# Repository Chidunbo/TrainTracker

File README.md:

# TrainTracker
TrainTrackerHardware

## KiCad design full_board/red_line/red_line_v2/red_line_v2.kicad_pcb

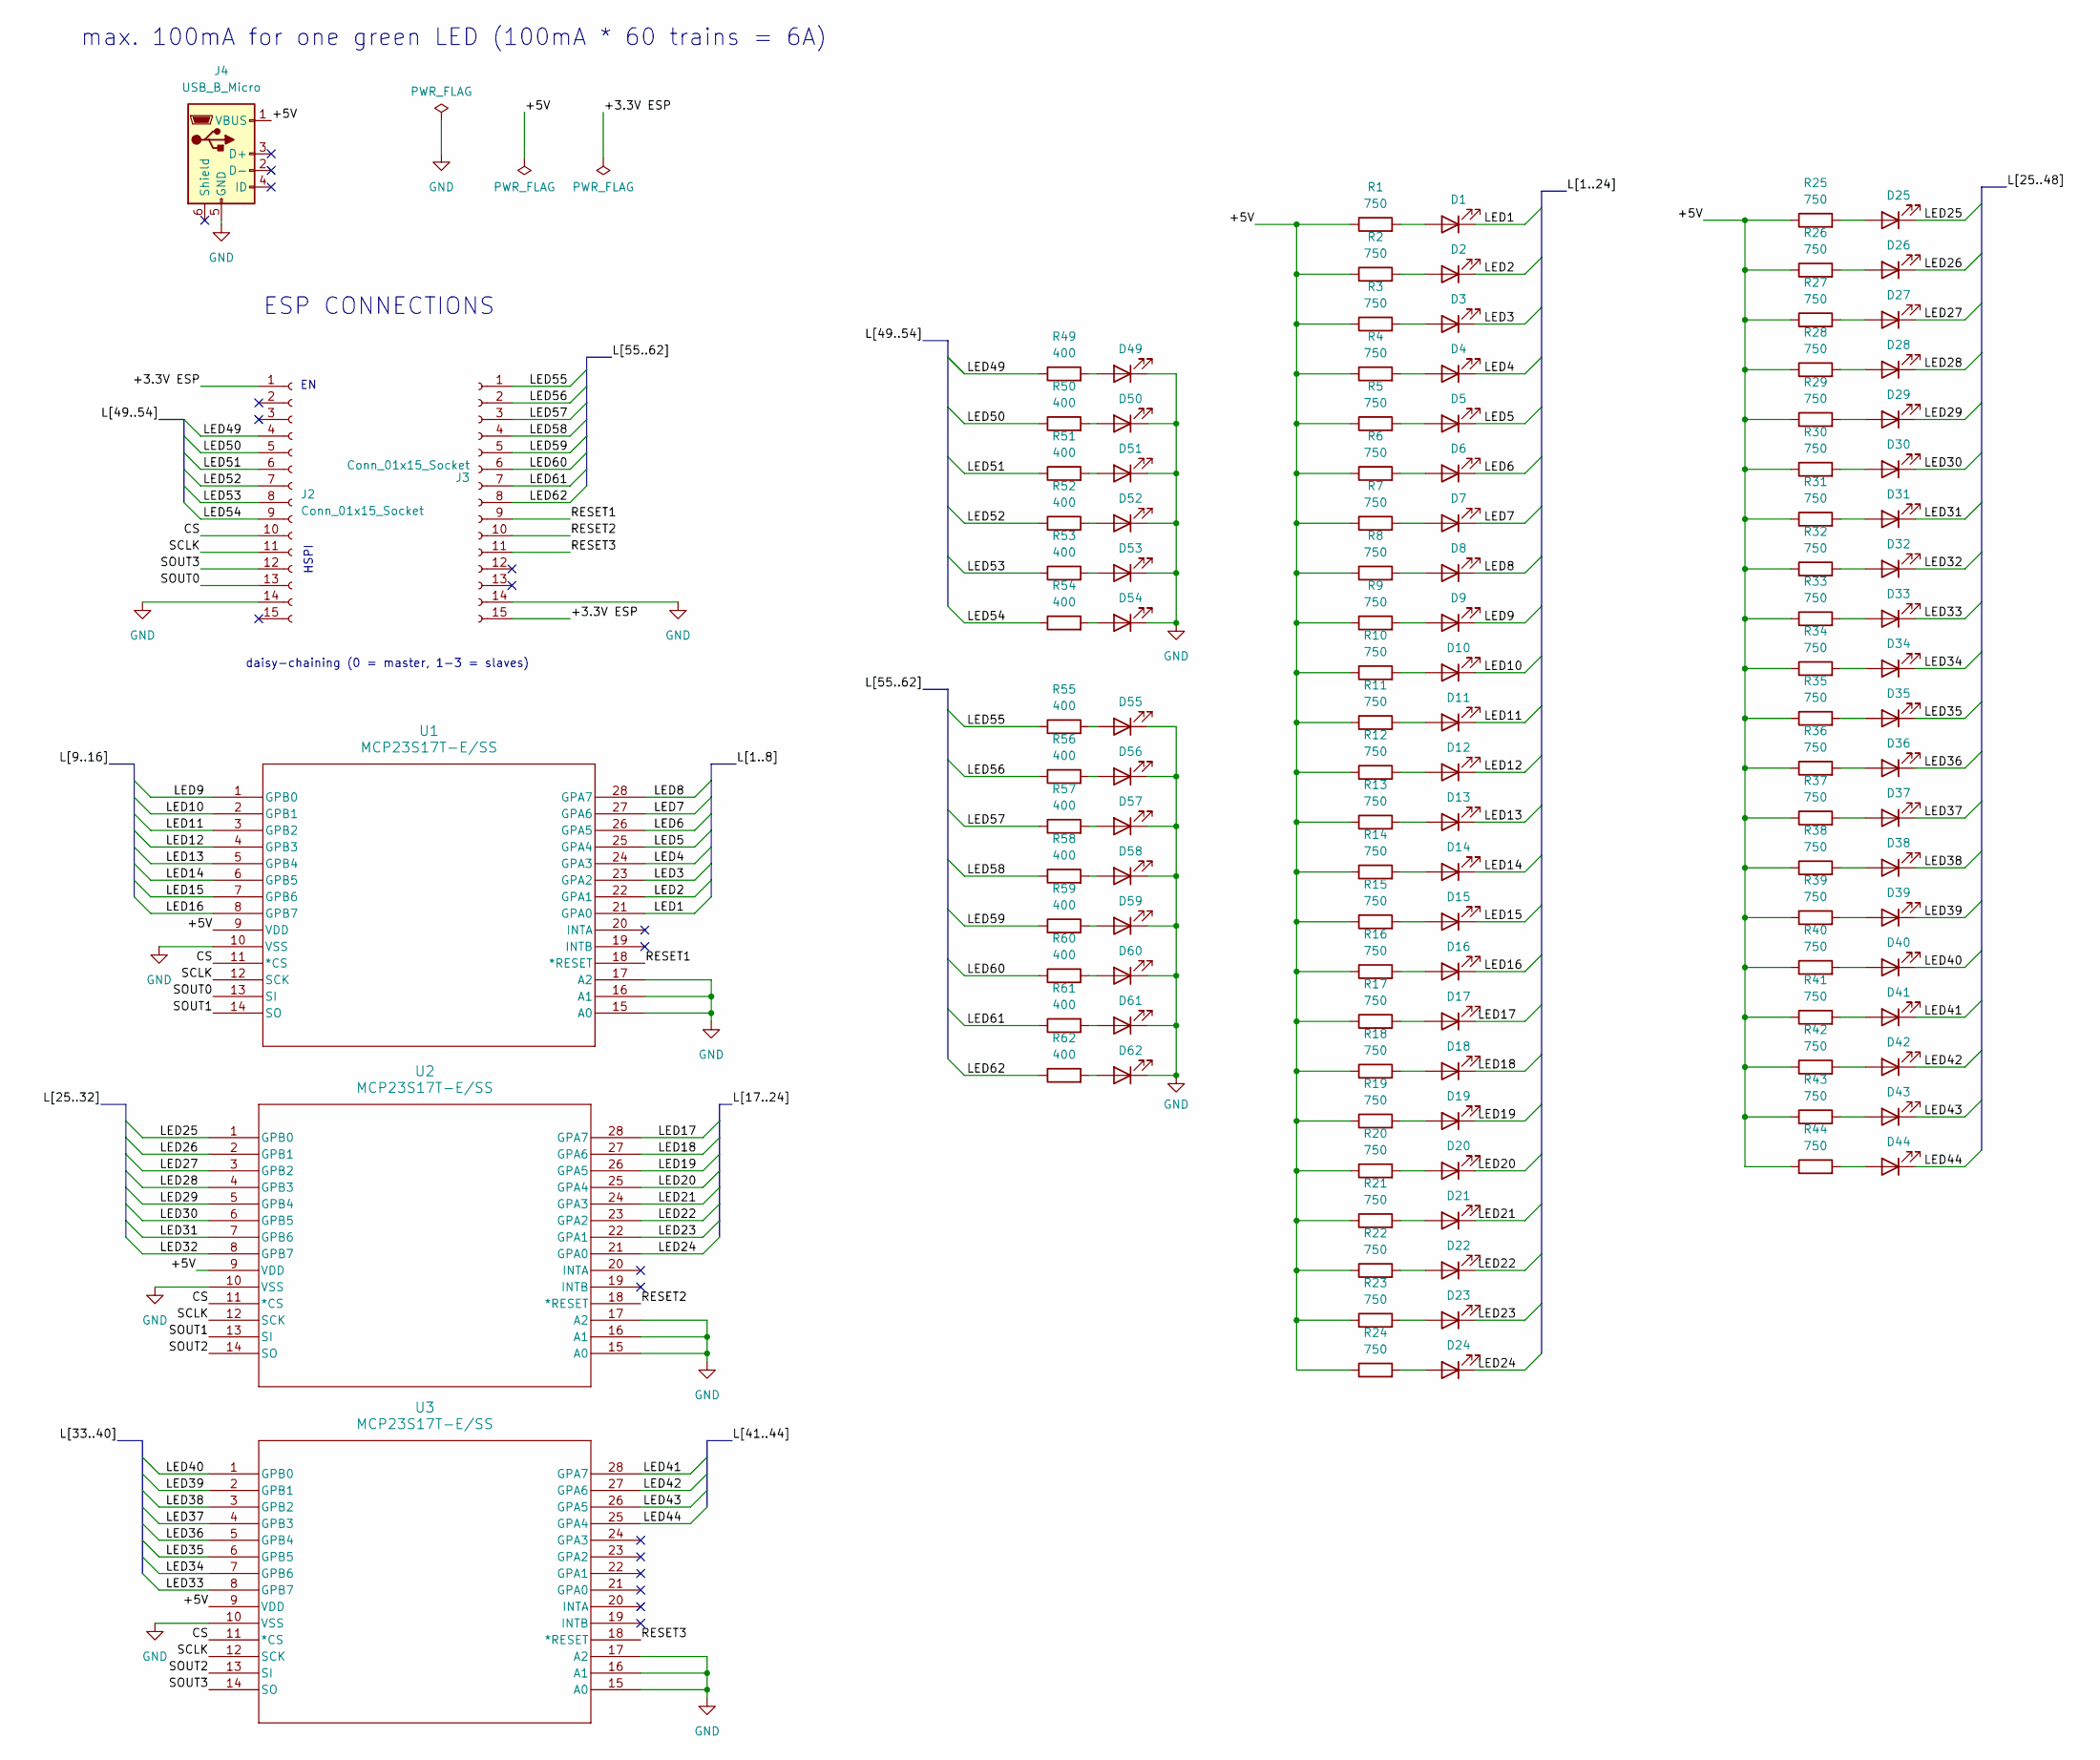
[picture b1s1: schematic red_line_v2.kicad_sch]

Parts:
D1, D2, D3, D4, D5, D6, D7, D8, D9, D10, D11, D12, D13, D14, D15, D16, D17, D18, D19, D20, D21, D22, D23, D24, D25, D26, D27, D28, D29, D30, D31, D32, D33, D34, D35, D36, D37, D38, D39, D40, D41, D42, D43, D44, D49, D50, D51, D52, D53, D54, D55, D56, D57, D58, D59, D60, D61, D62: LED; LED_0603_1608Metric
J2, J3: Conn_01x15_Socket; PinHeader_1x15_P2.54mm_Vertical
J4: USB_B_Micro; USB_Micro-B_Molex-105017-0001
R1, R2, R3, R4, R5, R6, R7, R8, R9, R10, R11, R12, R13, R14, R15, R16, R17, R18, R19, R20, R21, R22, R23, R24, R25, R26, R27, R28, R29, R30, R31, R32, R33, R34, R35, R36, R37, R38, R39, R40, R41, R42, R43, R44: 750; R_0603_1608Metric
R49, R50, R51, R52, R53, R54, R55, R56, R57, R58, R59, R60, R61, R62: 400; R_0603_1608Metric
U1, U2, U3: MCP23S17T-E/SS; SSOP28_MC_MCH

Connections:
/+3.3V ESP: J2.1, J3.15
/+5V: J4.1 (VBUS), R1.1, R2.1, R3.1, R4.1, R5.1, R6.1, R7.1, R8.1, R9.1, R10.1, R11.1, R12.1, R13.1, R14.1, R15.1, R16.1, R17.1, R18.1, R19.1, R20.1, R21.1, R22.1, R23.1, R24.1, R25.1, R26.1, R27.1, R28.1, R29.1, R30.1, R31.1, R32.1, R33.1, R34.1, R35.1, R36.1, R37.1, R38.1, R39.1, R40.1, R41.1, R42.1, R43.1, R44.1, U1.9 (VDD), U2.9 (VDD), U3.9 (VDD)
/CS: J2.10, U1.11 (*CS), U2.11 (*CS), U3.11 (*CS)
/LED1: D1.1 (K), U1.21 (GPA0)
/LED2: D2.1 (K), U1.22 (GPA1)
/LED3: D3.1 (K), U1.23 (GPA2)
/LED4: D4.1 (K), U1.24 (GPA3)
/LED5: D5.1 (K), U1.25 (GPA4)
/LED6: D6.1 (K), U1.26 (GPA5)
/LED7: D7.1 (K), U1.27 (GPA6)
/LED8: D8.1 (K), U1.28 (GPA7)
/LED9: D9.1 (K), U1.1 (GPB0)
/LED10: D10.1 (K), U1.2 (GPB1)
/LED11: D11.1 (K), U1.3 (GPB2)
/LED12: D12.1 (K), U1.4 (GPB3)
/LED13: D13.1 (K), U1.5 (GPB4)
/LED14: D14.1 (K), U1.6 (GPB5)
/LED15: D15.1 (K), U1.7 (GPB6)
/LED16: D16.1 (K), U1.8 (GPB7)
/LED17: D17.1 (K), U2.28 (GPA7)
/LED18: D18.1 (K), U2.27 (GPA6)
/LED19: D19.1 (K), U2.26 (GPA5)
/LED20: D20.1 (K), U2.25 (GPA4)
/LED21: D21.1 (K), U2.24 (GPA3)
/LED22: D22.1 (K), U2.23 (GPA2)
/LED23: D23.1 (K), U2.22 (GPA1)
/LED24: D24.1 (K), U2.21 (GPA0)
/LED25: D25.1 (K), U2.1 (GPB0)
/LED26: D26.1 (K), U2.2 (GPB1)
/LED27: D27.1 (K), U2.3 (GPB2)
/LED28: D28.1 (K), U2.4 (GPB3)
/LED29: D29.1 (K), U2.5 (GPB4)
/LED30: D30.1 (K), U2.6 (GPB5)
/LED31: D31.1 (K), U2.7 (GPB6)
/LED32: D32.1 (K), U2.8 (GPB7)
/LED33: D33.1 (K), U3.8 (GPB7)
/LED34: D34.1 (K), U3.7 (GPB6)
/LED35: D35.1 (K), U3.6 (GPB5)
/LED36: D36.1 (K), U3.5 (GPB4)
/LED37: D37.1 (K), U3.4 (GPB3)
/LED38: D38.1 (K), U3.3 (GPB2)
/LED39: D39.1 (K), U3.2 (GPB1)
/LED40: D40.1 (K), U3.1 (GPB0)
/LED41: D41.1 (K), U3.28 (GPA7)
/LED42: D42.1 (K), U3.27 (GPA6)
/LED43: D43.1 (K), U3.26 (GPA5)
/LED44: D44.1 (K), U3.25 (GPA4)
/LED49: J2.4, R49.1
/LED50: J2.5, R50.1
/LED51: J2.6, R51.1
/LED52: J2.7, R52.1
/LED53: J2.8, R53.1
/LED54: J2.9, R54.1
/LED55: J3.1, R55.1
/LED56: J3.2, R56.1
/LED57: J3.3, R57.1
/LED58: J3.4, R58.1
/LED59: J3.5, R59.1
/LED60: J3.6, R60.1
/LED61: J3.7, R61.1
/LED62: J3.8, R62.1
/RESET1: J3.9, U1.18 (*RESET)
/RESET2: J3.10, U2.18 (*RESET)
/RESET3: J3.11, U3.18 (*RESET)
/SCLK: J2.11, U1.12 (SCK), U2.12 (SCK), U3.12 (SCK)
/SOUT0: J2.13, U1.13 (SI)
/SOUT1: U1.14 (SO), U2.13 (SI)
/SOUT2: U2.14 (SO), U3.13 (SI)
/SOUT3: J2.12, U3.14 (SO)
GND: D49.1 (K), D50.1 (K), D51.1 (K), D52.1 (K), D53.1 (K), D54.1 (K), D55.1 (K), D56.1 (K), D57.1 (K), D58.1 (K), D59.1 (K), D60.1 (K), D61.1 (K), D62.1 (K), J2.14, J3.14, J4.5 (GND), U1.10 (VSS), U1.15 (A0), U1.16 (A1), U1.17 (A2), U2.10 (VSS), U2.15 (A0), U2.16 (A1), U2.17 (A2), U3.10 (VSS), U3.15 (A0), U3.16 (A1), U3.17 (A2)
unnamed: D1.2 (A), R1.2
unnamed: D2.2 (A), R2.2
unnamed: D3.2 (A), R3.2
unnamed: D4.2 (A), R4.2
unnamed: D5.2 (A), R5.2
unnamed: D6.2 (A), R6.2
unnamed: D7.2 (A), R7.2
unnamed: D8.2 (A), R8.2
unnamed: D9.2 (A), R9.2
unnamed: D10.2 (A), R10.2
unnamed: D11.2 (A), R11.2
unnamed: D12.2 (A), R12.2
unnamed: D13.2 (A), R13.2
unnamed: D14.2 (A), R14.2
unnamed: D15.2 (A), R15.2
unnamed: D16.2 (A), R16.2
unnamed: D17.2 (A), R17.2
unnamed: D18.2 (A), R18.2
unnamed: D19.2 (A), R19.2
unnamed: D20.2 (A), R20.2
unnamed: D21.2 (A), R21.2
unnamed: D22.2 (A), R22.2
unnamed: D23.2 (A), R23.2
unnamed: D24.2 (A), R24.2
unnamed: D25.2 (A), R25.2
unnamed: D26.2 (A), R26.2
unnamed: D27.2 (A), R27.2
unnamed: D28.2 (A), R28.2
unnamed: D29.2 (A), R29.2
unnamed: D30.2 (A), R30.2
unnamed: D31.2 (A), R31.2
unnamed: D32.2 (A), R32.2
unnamed: D33.2 (A), R33.2
unnamed: D34.2 (A), R34.2
unnamed: D35.2 (A), R35.2
unnamed: D36.2 (A), R36.2
unnamed: D37.2 (A), R37.2
unnamed: D38.2 (A), R38.2
unnamed: D39.2 (A), R39.2
unnamed: D40.2 (A), R40.2
unnamed: D41.2 (A), R41.2
unnamed: D42.2 (A), R42.2
unnamed: D43.2 (A), R43.2
unnamed: D44.2 (A), R44.2
unnamed: D49.2 (A), R49.2
unnamed: D50.2 (A), R50.2
unnamed: D51.2 (A), R51.2
unnamed: D52.2 (A), R52.2
unnamed: D53.2 (A), R53.2
unnamed: D54.2 (A), R54.2
unnamed: D55.2 (A), R55.2
unnamed: D56.2 (A), R56.2
unnamed: D57.2 (A), R57.2
unnamed: D58.2 (A), R58.2
unnamed: D59.2 (A), R59.2
unnamed: D60.2 (A), R60.2
unnamed: D61.2 (A), R61.2
unnamed: D62.2 (A), R62.2

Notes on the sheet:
HSPI
max. 100mA for one green LED (100mA * 60 trains = 6A)
ESP CONNECTIONS
daisy-chaining (0 = master, 1-3 = slaves)

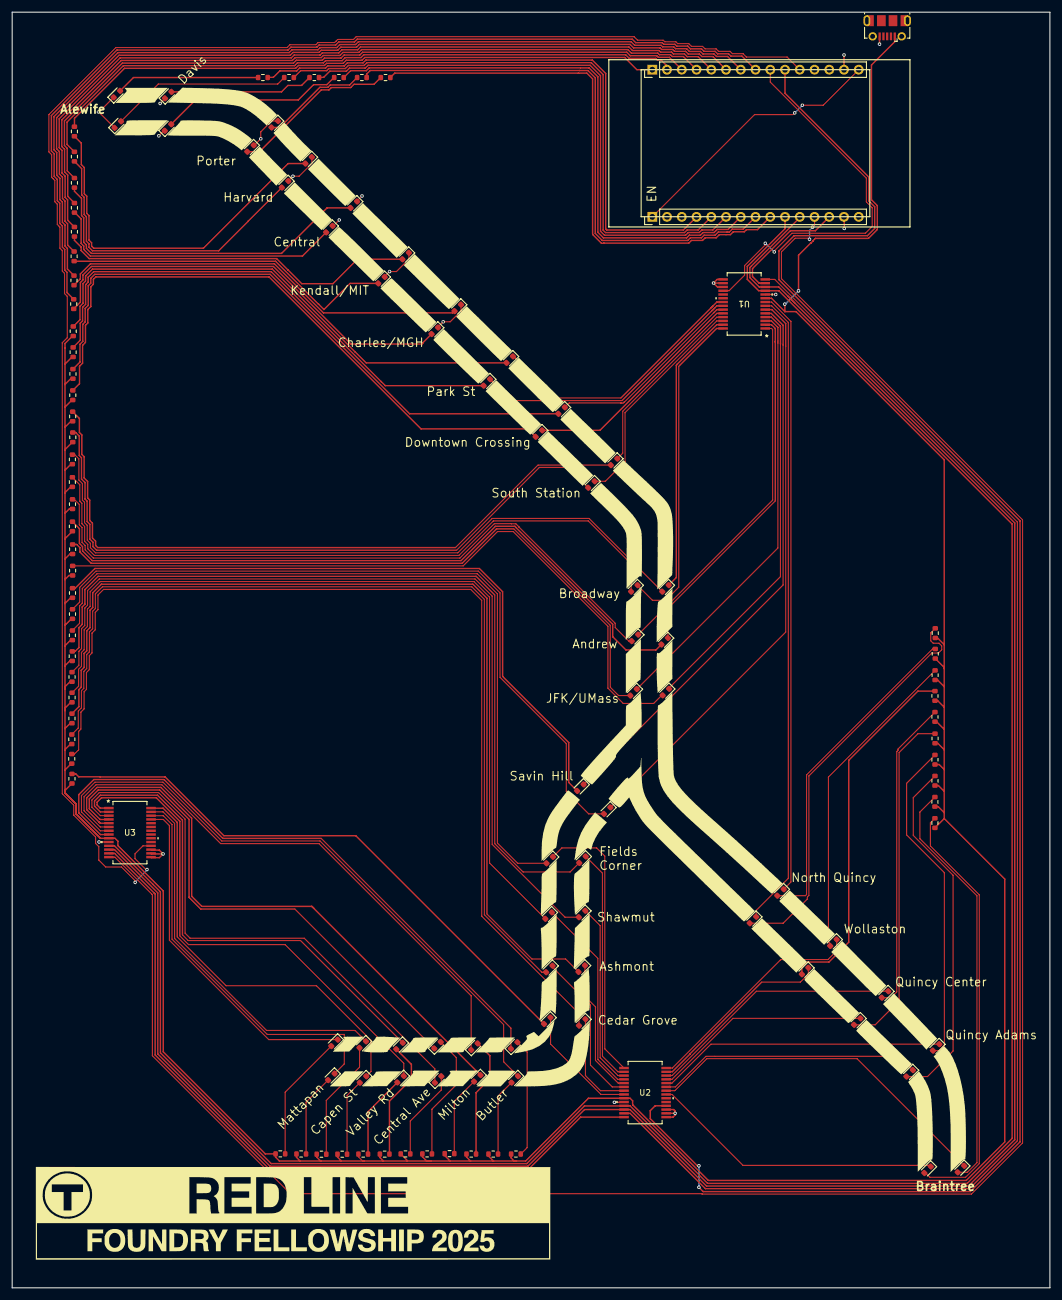
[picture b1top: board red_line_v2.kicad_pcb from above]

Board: 2 copper layers, 178.7 x 219.7 mm, 122 parts (0 on the bottom side), 128 nets.

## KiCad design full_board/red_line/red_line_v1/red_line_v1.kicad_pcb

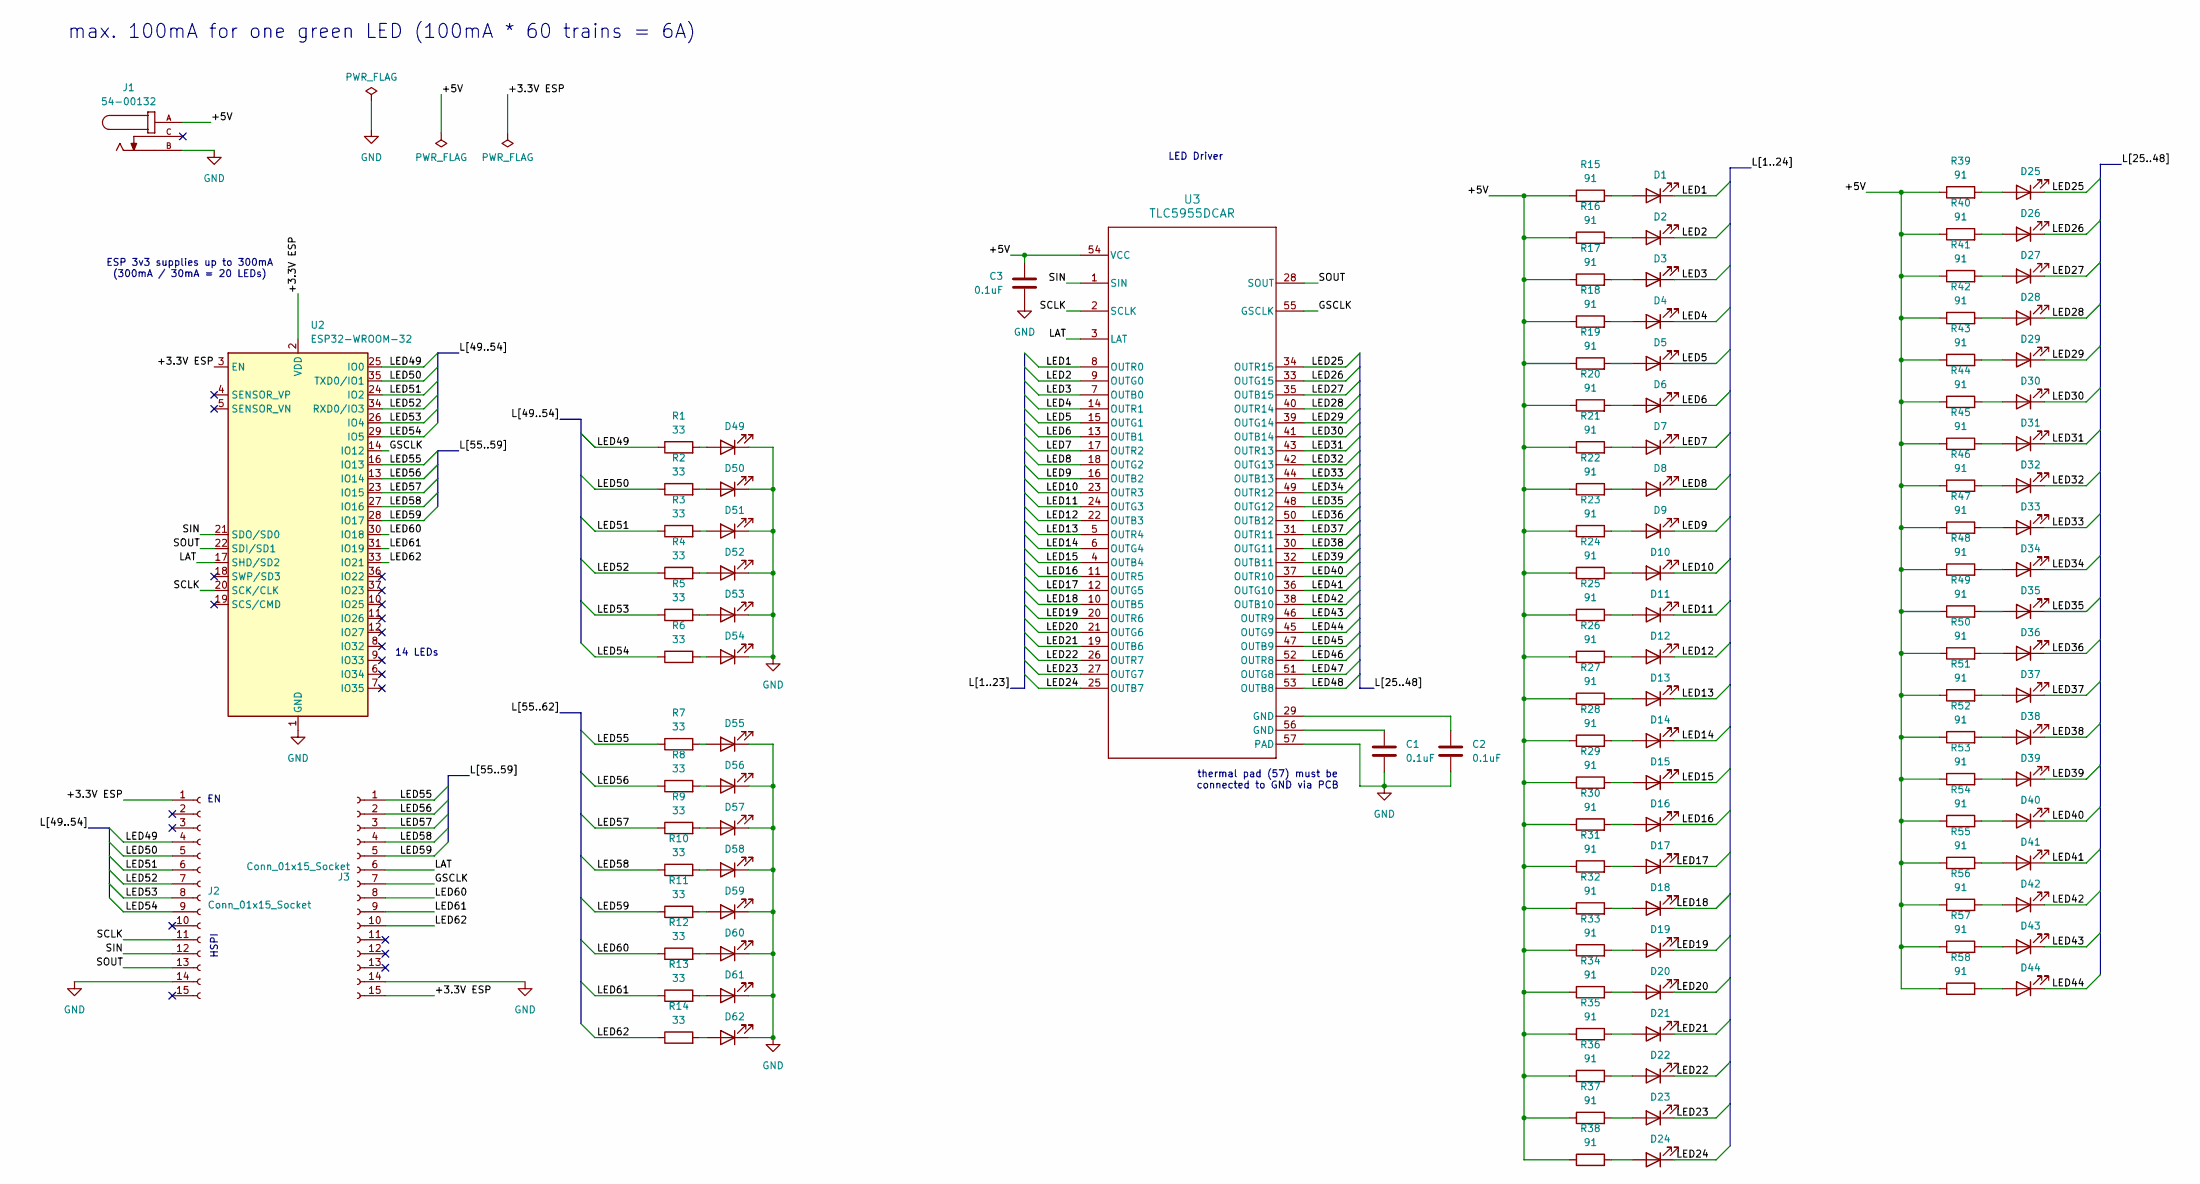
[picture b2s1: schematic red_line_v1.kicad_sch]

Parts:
C1, C2, C3: 0.1uF; C_0603
D1, D2, D3, D4, D5, D6, D7, D8, D9, D10, D11, D12, D13, D14, D15, D16, D17, D18, D19, D20, D21, D22, D23, D24, D25, D26, D27, D28, D29, D30, D31, D32, D33, D34, D35, D36, D37, D38, D39, D40, D41, D42, D43, D44, D49, D50, D51, D52, D53, D54, D55, D56, D57, D58, D59, D60, D61, D62: LED; LED_0603_1608Metric
J1: 54-00132; TENSILITY_54-00132; PARTREV A
J2, J3: Conn_01x15_Socket; PinHeader_1x15_P2.54mm_Vertical
R1, R2, R3, R4, R5, R6, R7, R8, R9, R10, R11, R12, R13, R14: 33; R_Axial_DIN0207_L6.3mm_D2.5mm_P2.54mm_Vertical
R15, R16, R17, R18, R19, R20, R21, R22, R23, R24, R25, R26, R27, R28, R29, R30, R31, R32, R33, R34, R35, R36, R37, R38, R39, R40, R41, R42, R43, R44, R45, R46, R47, R48, R49, R50, R51, R52, R53, R54, R55, R56, R57, R58: 91; R_Axial_DIN0207_L6.3mm_D2.5mm_P2.54mm_Vertical
U2: ESP32-WROOM-32
U3: TLC5955DCAR; DCA0056F_N

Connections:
/+3.3V ESP: J2.1, J3.15, U2.2 (VDD), U2.3 (EN)
/+5V: C3.2, J1.A, R15.1, R16.1, R17.1, R18.1, R19.1, R20.1, R21.1, R22.1, R23.1, R24.1, R25.1, R26.1, R27.1, R28.1, R29.1, R30.1, R31.1, R32.1, R33.1, R34.1, R35.1, R36.1, R37.1, R38.1, R39.1, R40.1, R41.1, R42.1, R43.1, R44.1, R45.1, R46.1, R47.1, R48.1, R49.1, R50.1, R51.1, R52.1, R53.1, R54.1, R55.1, R56.1, R57.1, R58.1, U3.54 (VCC)
/GSCLK: J3.7, U2.14 (IO12), U3.55 (GSCLK)
/LAT: J3.6, U2.17 (SHD/SD2), U3.3 (LAT)
/LED1: D1.1 (K), U3.8 (OUTR0)
/LED2: D2.1 (K), U3.9 (OUTG0)
/LED3: D3.1 (K), U3.7 (OUTB0)
/LED4: D4.1 (K), U3.14 (OUTR1)
/LED5: D5.1 (K), U3.15 (OUTG1)
/LED6: D6.1 (K), U3.13 (OUTB1)
/LED7: D7.1 (K), U3.17 (OUTR2)
/LED8: D8.1 (K), U3.18 (OUTG2)
/LED9: D9.1 (K), U3.16 (OUTB2)
/LED10: D10.1 (K), U3.23 (OUTR3)
/LED11: D11.1 (K), U3.24 (OUTG3)
/LED12: D12.1 (K), U3.22 (OUTB3)
/LED13: D13.1 (K), U3.5 (OUTR4)
/LED14: D14.1 (K), U3.6 (OUTG4)
/LED15: D15.1 (K), U3.4 (OUTB4)
/LED16: D16.1 (K), U3.11 (OUTR5)
/LED17: D17.1 (K), U3.12 (OUTG5)
/LED18: D18.1 (K), U3.10 (OUTB5)
/LED19: D19.1 (K), U3.20 (OUTR6)
/LED20: D20.1 (K), U3.21 (OUTG6)
/LED21: D21.1 (K), U3.19 (OUTB6)
/LED22: D22.1 (K), U3.26 (OUTR7)
/LED23: D23.1 (K), U3.27 (OUTG7)
/LED24: D24.1 (K), U3.25 (OUTB7)
/LED25: D25.1 (K), U3.34 (OUTR15)
/LED26: D26.1 (K), U3.33 (OUTG15)
/LED27: D27.1 (K), U3.35 (OUTB15)
/LED28: D28.1 (K), U3.40 (OUTR14)
/LED29: D29.1 (K), U3.39 (OUTG14)
/LED30: D30.1 (K), U3.41 (OUTB14)
/LED31: D31.1 (K), U3.43 (OUTR13)
/LED32: D32.1 (K), U3.42 (OUTG13)
/LED33: D33.1 (K), U3.44 (OUTB13)
/LED34: D34.1 (K), U3.49 (OUTR12)
/LED35: D35.1 (K), U3.48 (OUTG12)
/LED36: D36.1 (K), U3.50 (OUTB12)
/LED37: D37.1 (K), U3.31 (OUTR11)
/LED38: D38.1 (K), U3.30 (OUTG11)
/LED39: D39.1 (K), U3.32 (OUTB11)
/LED40: D40.1 (K), U3.37 (OUTR10)
/LED41: D41.1 (K), U3.36 (OUTG10)
/LED42: D42.1 (K), U3.38 (OUTB10)
/LED43: D43.1 (K), U3.46 (OUTR9)
/LED44: D44.1 (K), U3.45 (OUTG9)
/LED45: U3.47 (OUTB9)
/LED46: U3.52 (OUTR8)
/LED47: U3.51 (OUTG8)
/LED48: U3.53 (OUTB8)
/LED49: J2.4, R1.1, U2.25 (IO0)
/LED50: J2.5, R2.1, U2.35 (TXD0/IO1)
/LED51: J2.6, R3.1, U2.24 (IO2)
/LED52: J2.7, R4.1, U2.34 (RXD0/IO3)
/LED53: J2.8, R5.1, U2.26 (IO4)
/LED54: J2.9, R6.1, U2.29 (IO5)
/LED55: J3.1, R7.1, U2.16 (IO13)
/LED56: J3.2, R8.1, U2.13 (IO14)
/LED57: J3.3, R9.1, U2.23 (IO15)
/LED58: J3.4, R10.1, U2.27 (IO16)
/LED59: J3.5, R11.1, U2.28 (IO17)
/LED60: J3.8, R12.1, U2.30 (IO18)
/LED61: J3.9, R13.1, U2.31 (IO19)
/LED62: J3.10, R14.1, U2.33 (IO21)
/SCLK: J2.11, U2.20 (SCK/CLK), U3.2 (SCLK)
/SIN: J2.12, U2.21 (SDO/SD0), U3.1 (SIN)
/SOUT: J2.13, U2.22 (SDI/SD1), U3.28 (SOUT)
GND: C1.1, C2.1, C3.1, D49.1 (K), D50.1 (K), D51.1 (K), D52.1 (K), D53.1 (K), D54.1 (K), D55.1 (K), D56.1 (K), D57.1 (K), D58.1 (K), D59.1 (K), D60.1 (K), D61.1 (K), D62.1 (K), J1.B, J2.14, J3.14, U2.1 (GND), U2.15 (GND), U2.38 (GND), U2.39 (GND), U3.57 (PAD)
unnamed: C1.2, U3.56 (GND)
unnamed: C2.2, U3.29 (GND)
unnamed: D1.2 (A), R15.2
unnamed: D2.2 (A), R16.2
unnamed: D3.2 (A), R17.2
unnamed: D4.2 (A), R18.2
unnamed: D5.2 (A), R19.2
unnamed: D6.2 (A), R20.2
unnamed: D7.2 (A), R21.2
unnamed: D8.2 (A), R22.2
unnamed: D9.2 (A), R23.2
unnamed: D10.2 (A), R24.2
unnamed: D11.2 (A), R25.2
unnamed: D12.2 (A), R26.2
unnamed: D13.2 (A), R27.2
unnamed: D14.2 (A), R28.2
unnamed: D15.2 (A), R29.2
unnamed: D16.2 (A), R30.2
unnamed: D17.2 (A), R31.2
unnamed: D18.2 (A), R32.2
unnamed: D19.2 (A), R33.2
unnamed: D20.2 (A), R34.2
unnamed: D21.2 (A), R35.2
unnamed: D22.2 (A), R36.2
unnamed: D23.2 (A), R37.2
unnamed: D24.2 (A), R38.2
unnamed: D25.2 (A), R39.2
unnamed: D26.2 (A), R40.2
unnamed: D27.2 (A), R41.2
unnamed: D28.2 (A), R42.2
unnamed: D29.2 (A), R43.2
unnamed: D30.2 (A), R44.2
unnamed: D31.2 (A), R45.2
unnamed: D32.2 (A), R46.2
unnamed: D33.2 (A), R47.2
unnamed: D34.2 (A), R48.2
unnamed: D35.2 (A), R49.2
unnamed: D36.2 (A), R50.2
unnamed: D37.2 (A), R51.2
unnamed: D38.2 (A), R52.2
unnamed: D39.2 (A), R53.2
unnamed: D40.2 (A), R54.2
unnamed: D41.2 (A), R55.2
unnamed: D42.2 (A), R56.2
unnamed: D43.2 (A), R57.2
unnamed: D44.2 (A), R58.2
unnamed: D49.2 (A), R1.2
unnamed: D50.2 (A), R2.2
unnamed: D51.2 (A), R3.2
unnamed: D52.2 (A), R4.2
unnamed: D53.2 (A), R5.2
unnamed: D54.2 (A), R6.2
unnamed: D55.2 (A), R7.2
unnamed: D56.2 (A), R8.2
unnamed: D57.2 (A), R9.2
unnamed: D58.2 (A), R10.2
unnamed: D59.2 (A), R11.2
unnamed: D60.2 (A), R12.2
unnamed: D61.2 (A), R13.2
unnamed: D62.2 (A), R14.2

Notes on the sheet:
HSPI
14 LEDs
max. 100mA for one green LED (100mA * 60 trains = 6A)
thermal pad (57) must be connected to GND via PCB
LED Driver
ESP 3v3 supplies up to 300mA (300mA / 30mA = 20 LEDs)

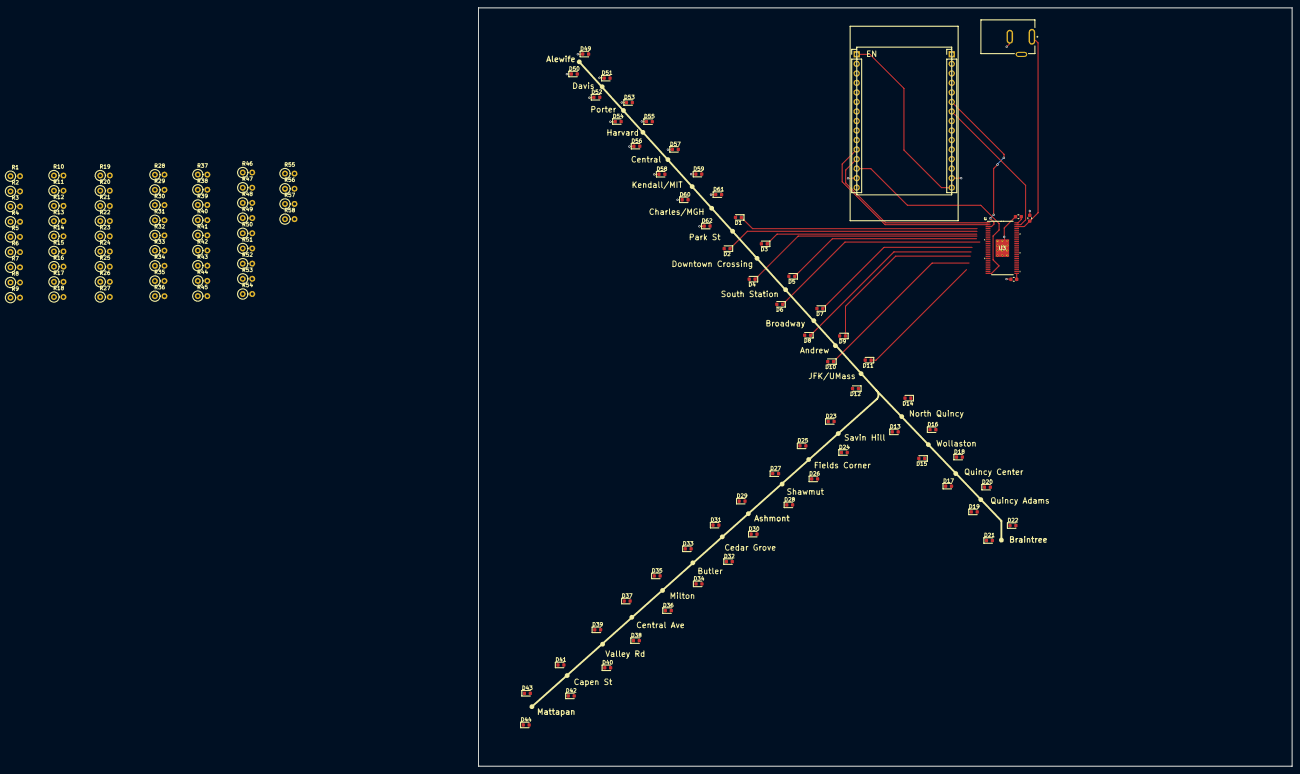
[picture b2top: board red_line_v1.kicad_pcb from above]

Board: 2 copper layers, 217.0 x 202.3 mm, 123 parts (0 on the bottom side), 126 nets.

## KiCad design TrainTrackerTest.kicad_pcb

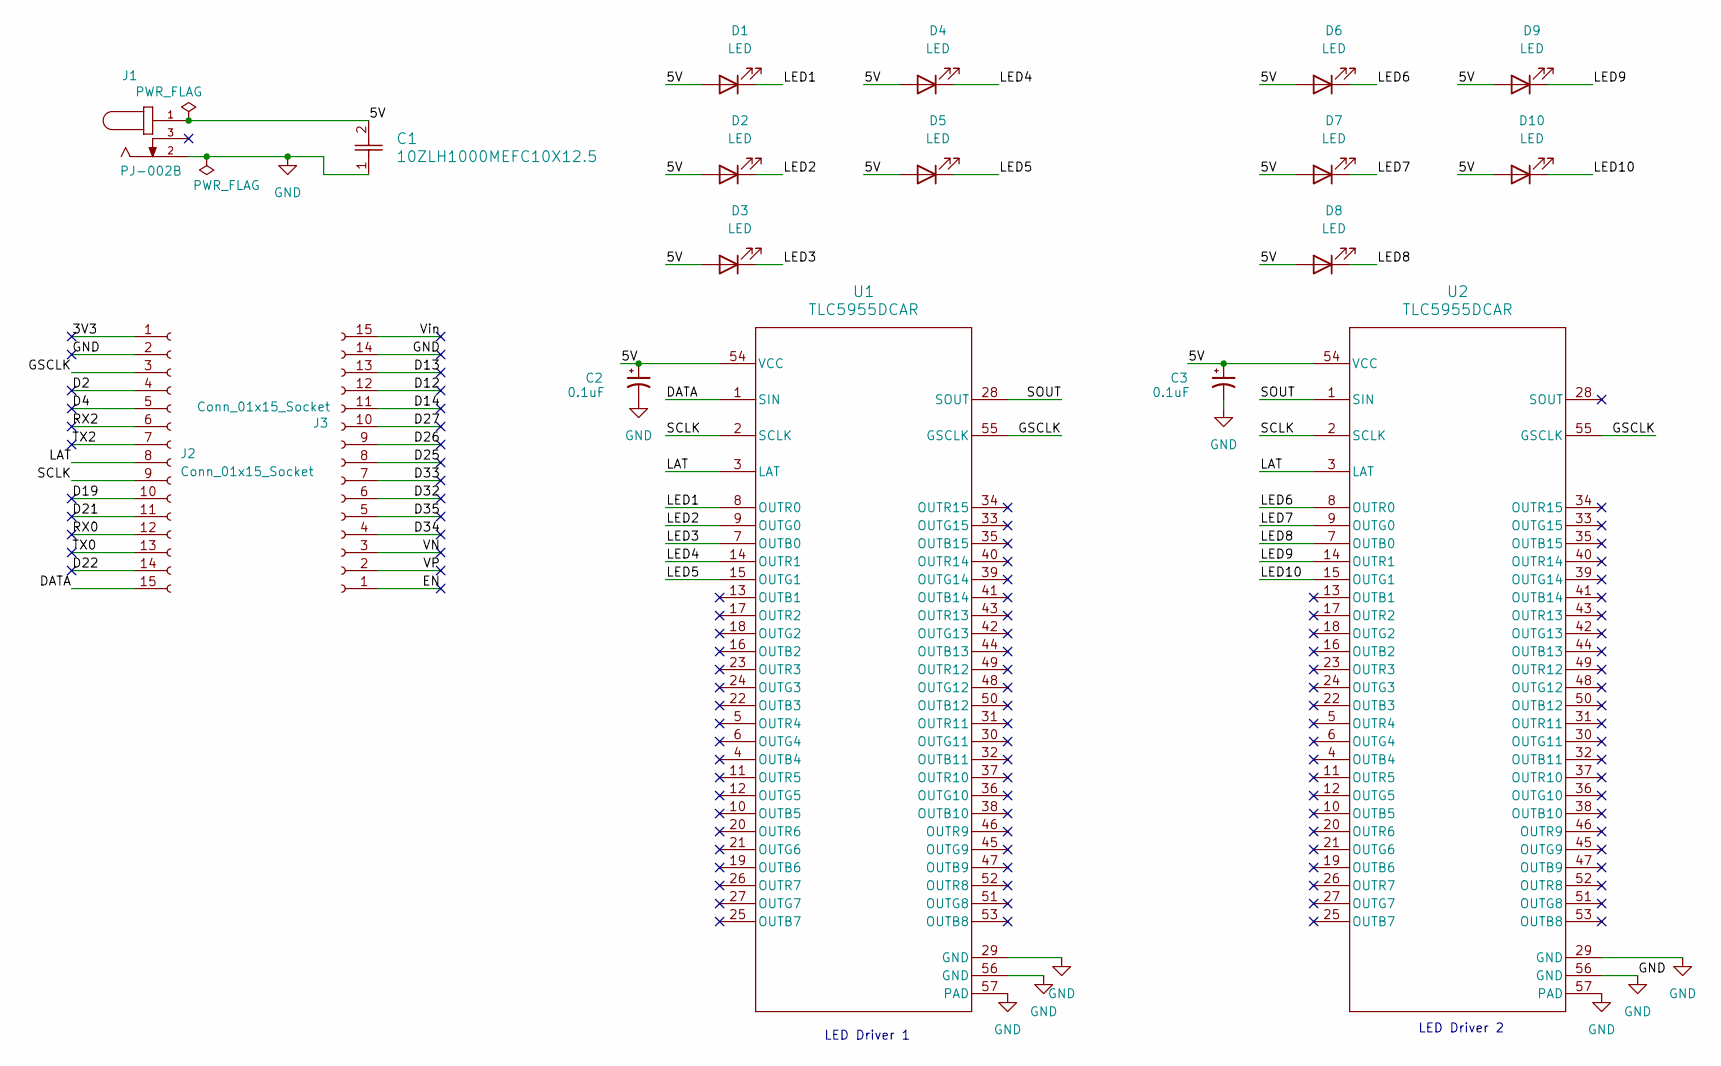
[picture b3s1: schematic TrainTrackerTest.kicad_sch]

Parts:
C1: 10ZLH1000MEFC10X12.5; CAP_10X12.5_RUB
C2, C3: 0.1uF; C_0603_1608Metric
D1, D2, D3, D4, D5, D6, D7, D8, D9, D10: LED; LED_0603_1608Metric
J1: PJ-002B; CUI_PJ-002B
J2, J3: Conn_01x15_Socket; PinHeader_1x15_P2.54mm_Vertical
U1, U2: TLC5955DCAR; DCA0056F_N

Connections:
/3V3: J2.1
/5V: C1.2, C2.1, C3.1, D1.2 (A), D2.2 (A), D3.2 (A), D4.2 (A), D5.2 (A), D6.2 (A), D7.2 (A), D8.2 (A), D9.2 (A), D10.2 (A), J1.1, U1.54 (VCC), U2.54 (VCC)
/D2: J2.4
/D4: J2.5
/D12: J3.12
/D13: J3.13
/D14: J3.11
/D19: J2.10
/D21: J2.11
/D22: J2.14
/D25: J3.8
/D26: J3.9
/D27: J3.10
/D32: J3.6
/D33: J3.7
/D34: J3.4
/D35: J3.5
/DATA: J2.15, U1.1 (SIN)
/EN: J3.1
/GSCLK: J2.3, U1.55 (GSCLK), U2.55 (GSCLK)
/LAT: J2.8, U1.3 (LAT), U2.3 (LAT)
/LED1: D1.1 (K), U1.8 (OUTR0)
/LED2: D2.1 (K), U1.9 (OUTG0)
/LED3: D3.1 (K), U1.7 (OUTB0)
/LED4: D4.1 (K), U1.14 (OUTR1)
/LED5: D5.1 (K), U1.15 (OUTG1)
/LED6: D6.1 (K), U2.8 (OUTR0)
/LED7: D7.1 (K), U2.9 (OUTG0)
/LED8: D8.1 (K), U2.7 (OUTB0)
/LED9: D9.1 (K), U2.14 (OUTR1)
/LED10: D10.1 (K), U2.15 (OUTG1)
/RX0: J2.12
/RX2: J2.6
/SCLK: J2.9, U1.2 (SCLK), U2.2 (SCLK)
/SOUT: U1.28 (SOUT), U2.1 (SIN)
/TX0: J2.13
/TX2: J2.7
/VN: J3.3
/VP: J3.2
/Vin: J3.15
GND: C1.1, C2.2, C3.2, J1.2, J2.2, J3.14, U1.29 (GND), U1.56 (GND), U1.57 (PAD), U1.V, U2.29 (GND), U2.56 (GND), U2.57 (PAD), U2.V

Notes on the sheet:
LED Driver 1
LED Driver 2

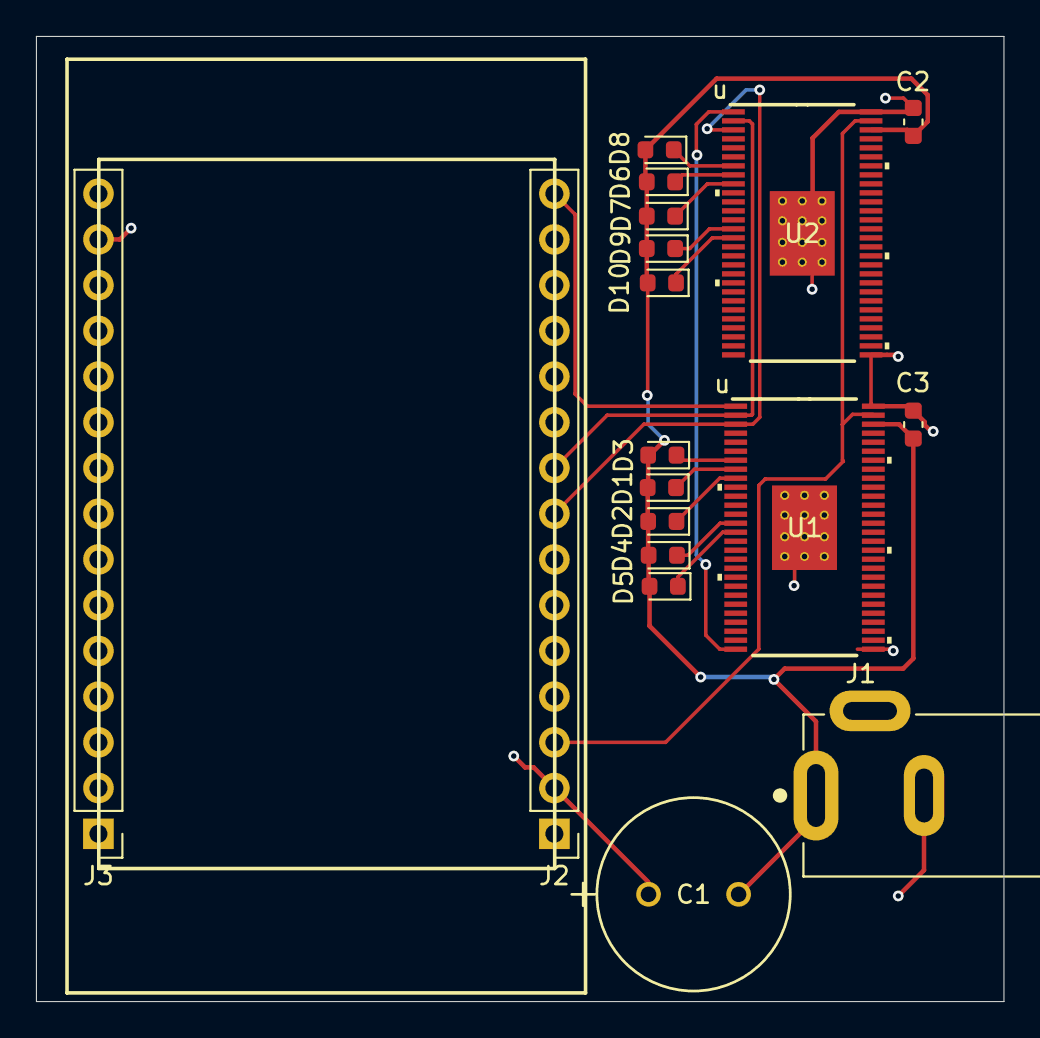
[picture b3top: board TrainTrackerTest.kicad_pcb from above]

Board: 2 copper layers, 53.8 x 53.6 mm, 18 parts (0 on the bottom side), 17 nets.

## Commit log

2025-02-25 FIrst draft unfinished
2025-02-26 Finish first draft of test board
2025-03-04 finish layout draft with some DRC failure
2025-03-05 Finalize test board pcb layout
2025-03-05 Finalized test board pcb layout
2025-03-07 Change 1000uF footprint
2025-03-11 New gerber zip file with finlaized part
2025-04-16 Finished red line laayout minus silkscreen
2025-04-18 add silkscreen, adjust layout
